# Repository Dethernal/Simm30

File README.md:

* 30 pin 16 MiB Simm module with optional parity chip

Fabrication files can be found in fab_simm30_16 directory.

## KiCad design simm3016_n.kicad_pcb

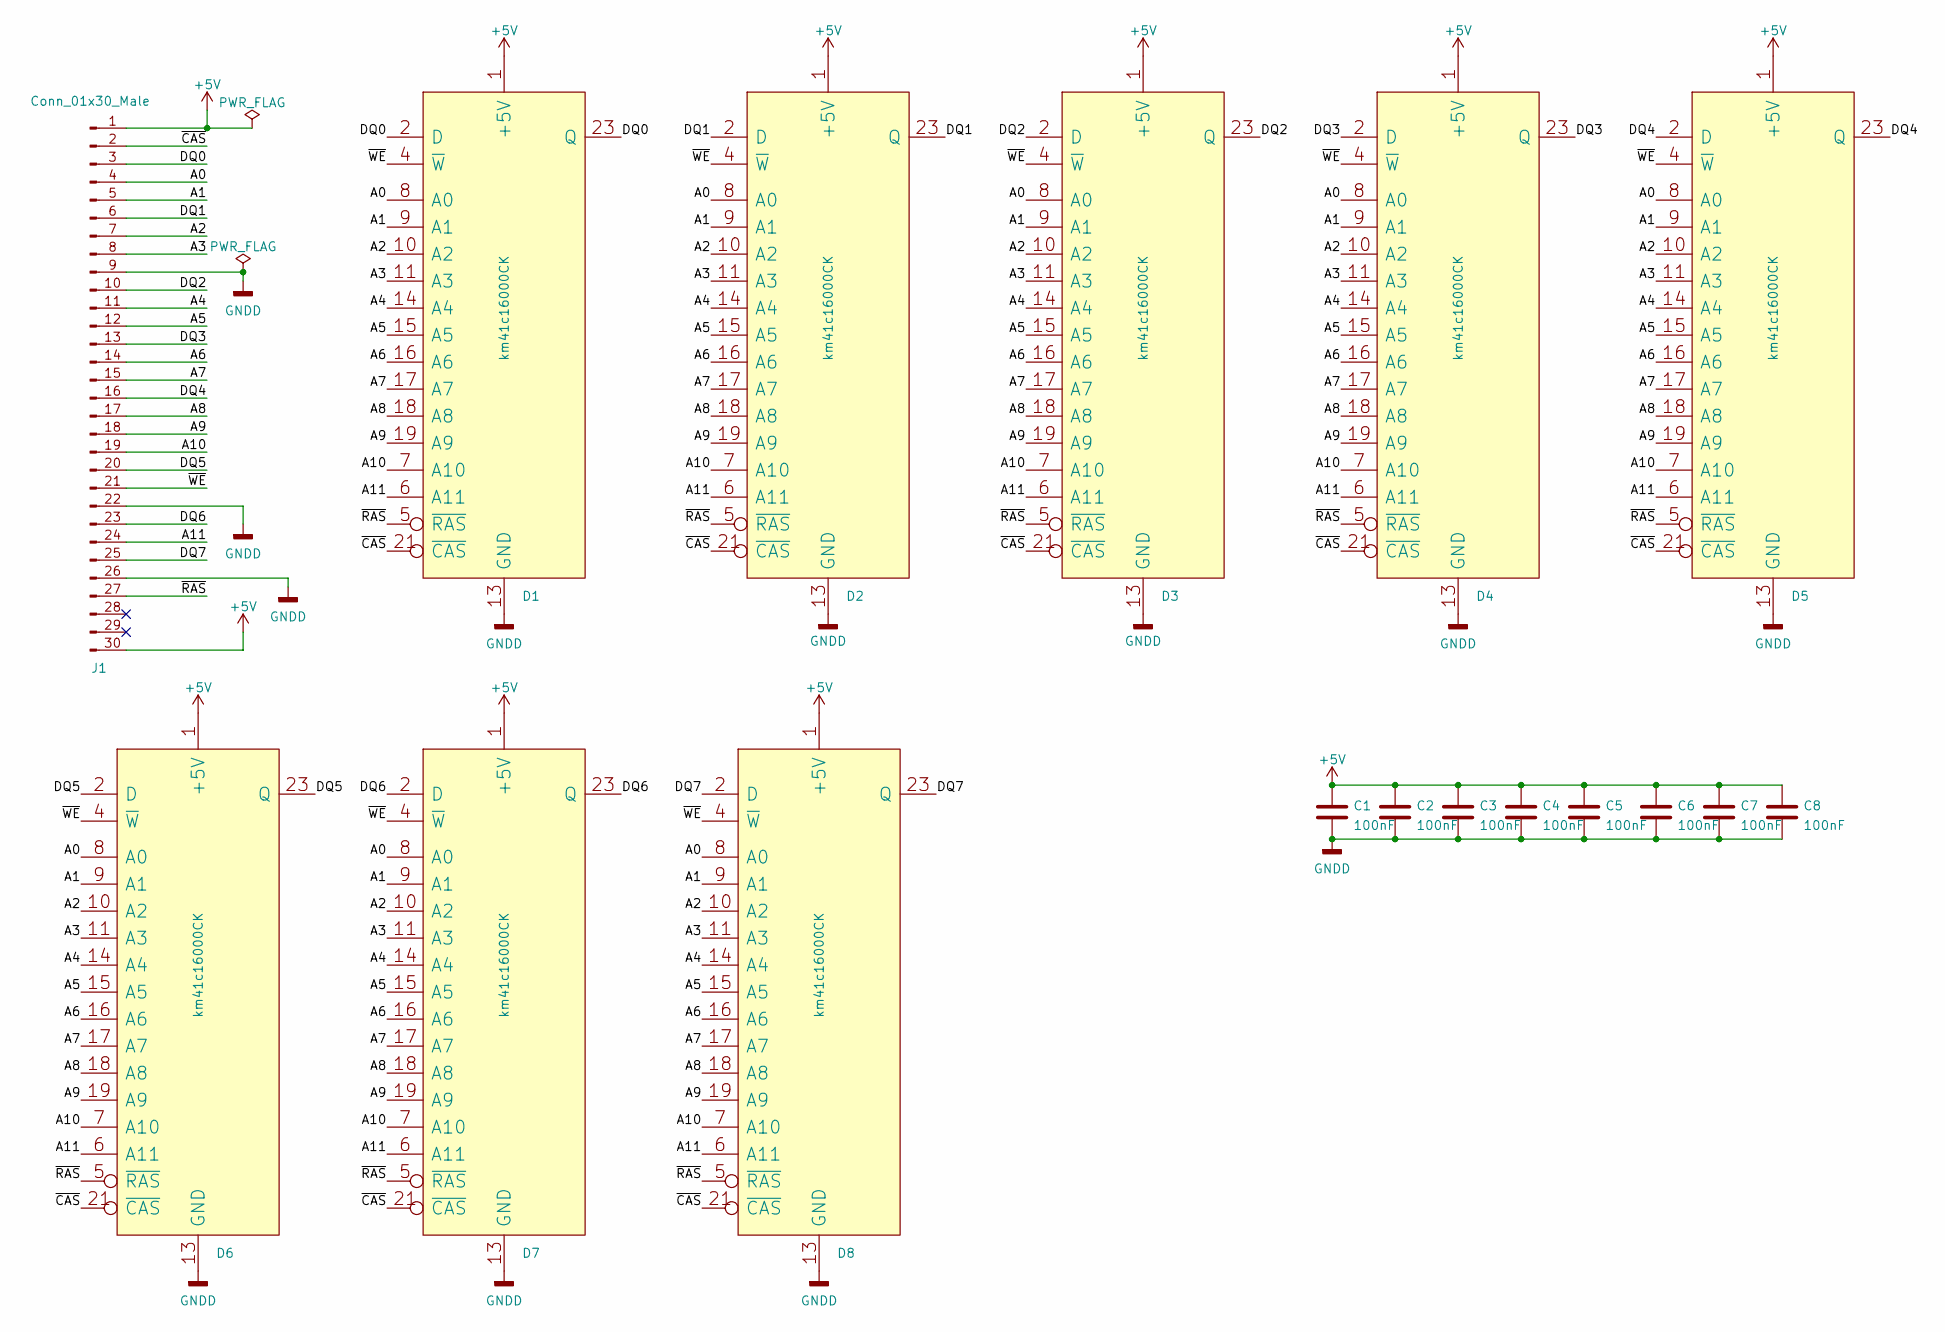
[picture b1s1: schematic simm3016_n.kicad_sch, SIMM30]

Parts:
C1, C2, C3, C4, C5, C6, C7, C8: 100nF; C_0805_2012Metric_Pad1.18x1.45mm_HandSolder
D1, D2, D3, D4, D5, D6, D7, D8: km41c16000CK; SOJ-26-24_7.62x17.14mm_P1.27mm
J1: Conn_01x30_Male; SIMM30_88.86mm_P2.54mm_Edge

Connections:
+5V: C1.1, C2.1, C3.1, C4.1, C5.1, C6.1, C7.1, C8.1, D1.1 (+5V), D2.1 (+5V), D3.1 (+5V), D4.1 (+5V), D5.1 (+5V), D6.1 (+5V), D7.1 (+5V), D8.1 (+5V), J1.1, J1.30
/A0: D1.8 (A0), D2.8 (A0), D3.8 (A0), D4.8 (A0), D5.8 (A0), D6.8 (A0), D7.8 (A0), D8.8 (A0), J1.4
/A1: D1.9 (A1), D2.9 (A1), D3.9 (A1), D4.9 (A1), D5.9 (A1), D6.9 (A1), D7.9 (A1), D8.9 (A1), J1.5
/A2: D1.10 (A2), D2.10 (A2), D3.10 (A2), D4.10 (A2), D5.10 (A2), D6.10 (A2), D7.10 (A2), D8.10 (A2), J1.7
/A3: D1.11 (A3), D2.11 (A3), D3.11 (A3), D4.11 (A3), D5.11 (A3), D6.11 (A3), D7.11 (A3), D8.11 (A3), J1.8
/A4: D1.14 (A4), D2.14 (A4), D3.14 (A4), D4.14 (A4), D5.14 (A4), D6.14 (A4), D7.14 (A4), D8.14 (A4), J1.11
/A5: D1.15 (A5), D2.15 (A5), D3.15 (A5), D4.15 (A5), D5.15 (A5), D6.15 (A5), D7.15 (A5), D8.15 (A5), J1.12
/A6: D1.16 (A6), D2.16 (A6), D3.16 (A6), D4.16 (A6), D5.16 (A6), D6.16 (A6), D7.16 (A6), D8.16 (A6), J1.14
/A7: D1.17 (A7), D2.17 (A7), D3.17 (A7), D4.17 (A7), D5.17 (A7), D6.17 (A7), D7.17 (A7), D8.17 (A7), J1.15
/A8: D1.18 (A8), D2.18 (A8), D3.18 (A8), D4.18 (A8), D5.18 (A8), D6.18 (A8), D7.18 (A8), D8.18 (A8), J1.17
/A9: D1.19 (A9), D2.19 (A9), D3.19 (A9), D4.19 (A9), D5.19 (A9), D6.19 (A9), D7.19 (A9), D8.19 (A9), J1.18
/A10: D1.7 (A10), D2.7 (A10), D3.7 (A10), D4.7 (A10), D5.7 (A10), D6.7 (A10), D7.7 (A10), D8.7 (A10), J1.19
/A11: D1.6 (A11), D2.6 (A11), D3.6 (A11), D4.6 (A11), D5.6 (A11), D6.6 (A11), D7.6 (A11), D8.6 (A11), J1.24
/DQ0: D1.2 (D), D1.23 (Q), J1.3
/DQ1: D2.2 (D), D2.23 (Q), J1.6
/DQ2: D3.2 (D), D3.23 (Q), J1.10
/DQ3: D4.2 (D), D4.23 (Q), J1.13
/DQ4: D5.2 (D), D5.23 (Q), J1.16
/DQ5: D6.2 (D), D6.23 (Q), J1.20
/DQ6: D7.2 (D), D7.23 (Q), J1.23
/DQ7: D8.2 (D), D8.23 (Q), J1.25
/~CAS: D1.21 (~CAS), D2.21 (~CAS), D3.21 (~CAS), D4.21 (~CAS), D5.21 (~CAS), D6.21 (~CAS), D7.21 (~CAS), D8.21 (~CAS), J1.2
/~RAS: D1.5 (~RAS), D2.5 (~RAS), D3.5 (~RAS), D4.5 (~RAS), D5.5 (~RAS), D6.5 (~RAS), D7.5 (~RAS), D8.5 (~RAS), J1.27
/~WE: D1.4 (~W), D2.4 (~W), D3.4 (~W), D4.4 (~W), D5.4 (~W), D6.4 (~W), D7.4 (~W), D8.4 (~W), J1.21
GNDD: C1.2, C2.2, C3.2, C4.2, C5.2, C6.2, C7.2, C8.2, D1.13 (GND), D2.13 (GND), D3.13 (GND), D4.13 (GND), D5.13 (GND), D6.13 (GND), D7.13 (GND), D8.13 (GND), J1.9, J1.22, J1.26

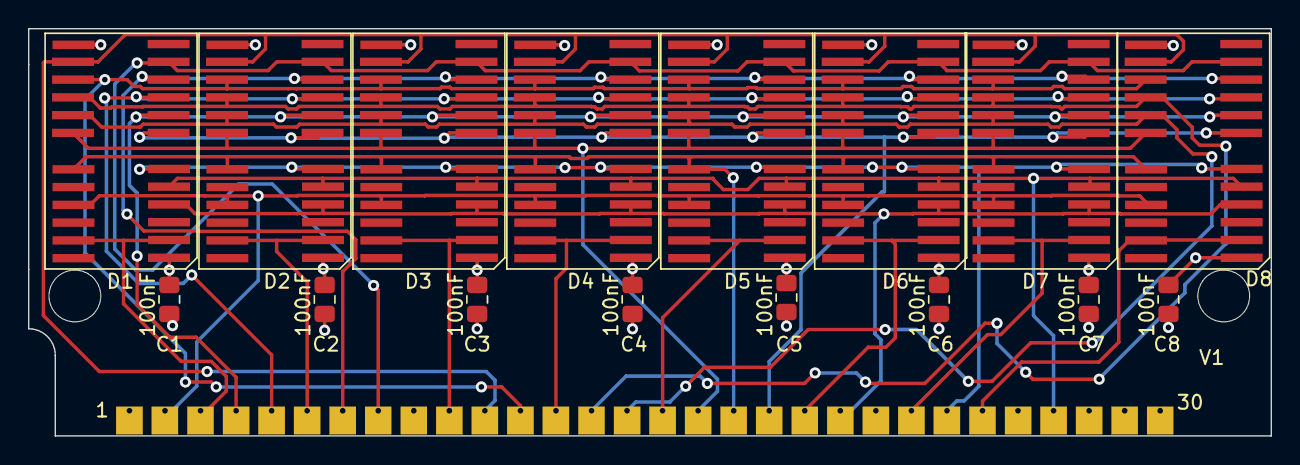
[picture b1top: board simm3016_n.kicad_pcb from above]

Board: 4 copper layers, 88.8 x 29.1 mm, 18 parts (1 on the bottom side), 25 nets.

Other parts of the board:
LOGO: OSHW-Logo2_9.8x8mm_SilkScreen

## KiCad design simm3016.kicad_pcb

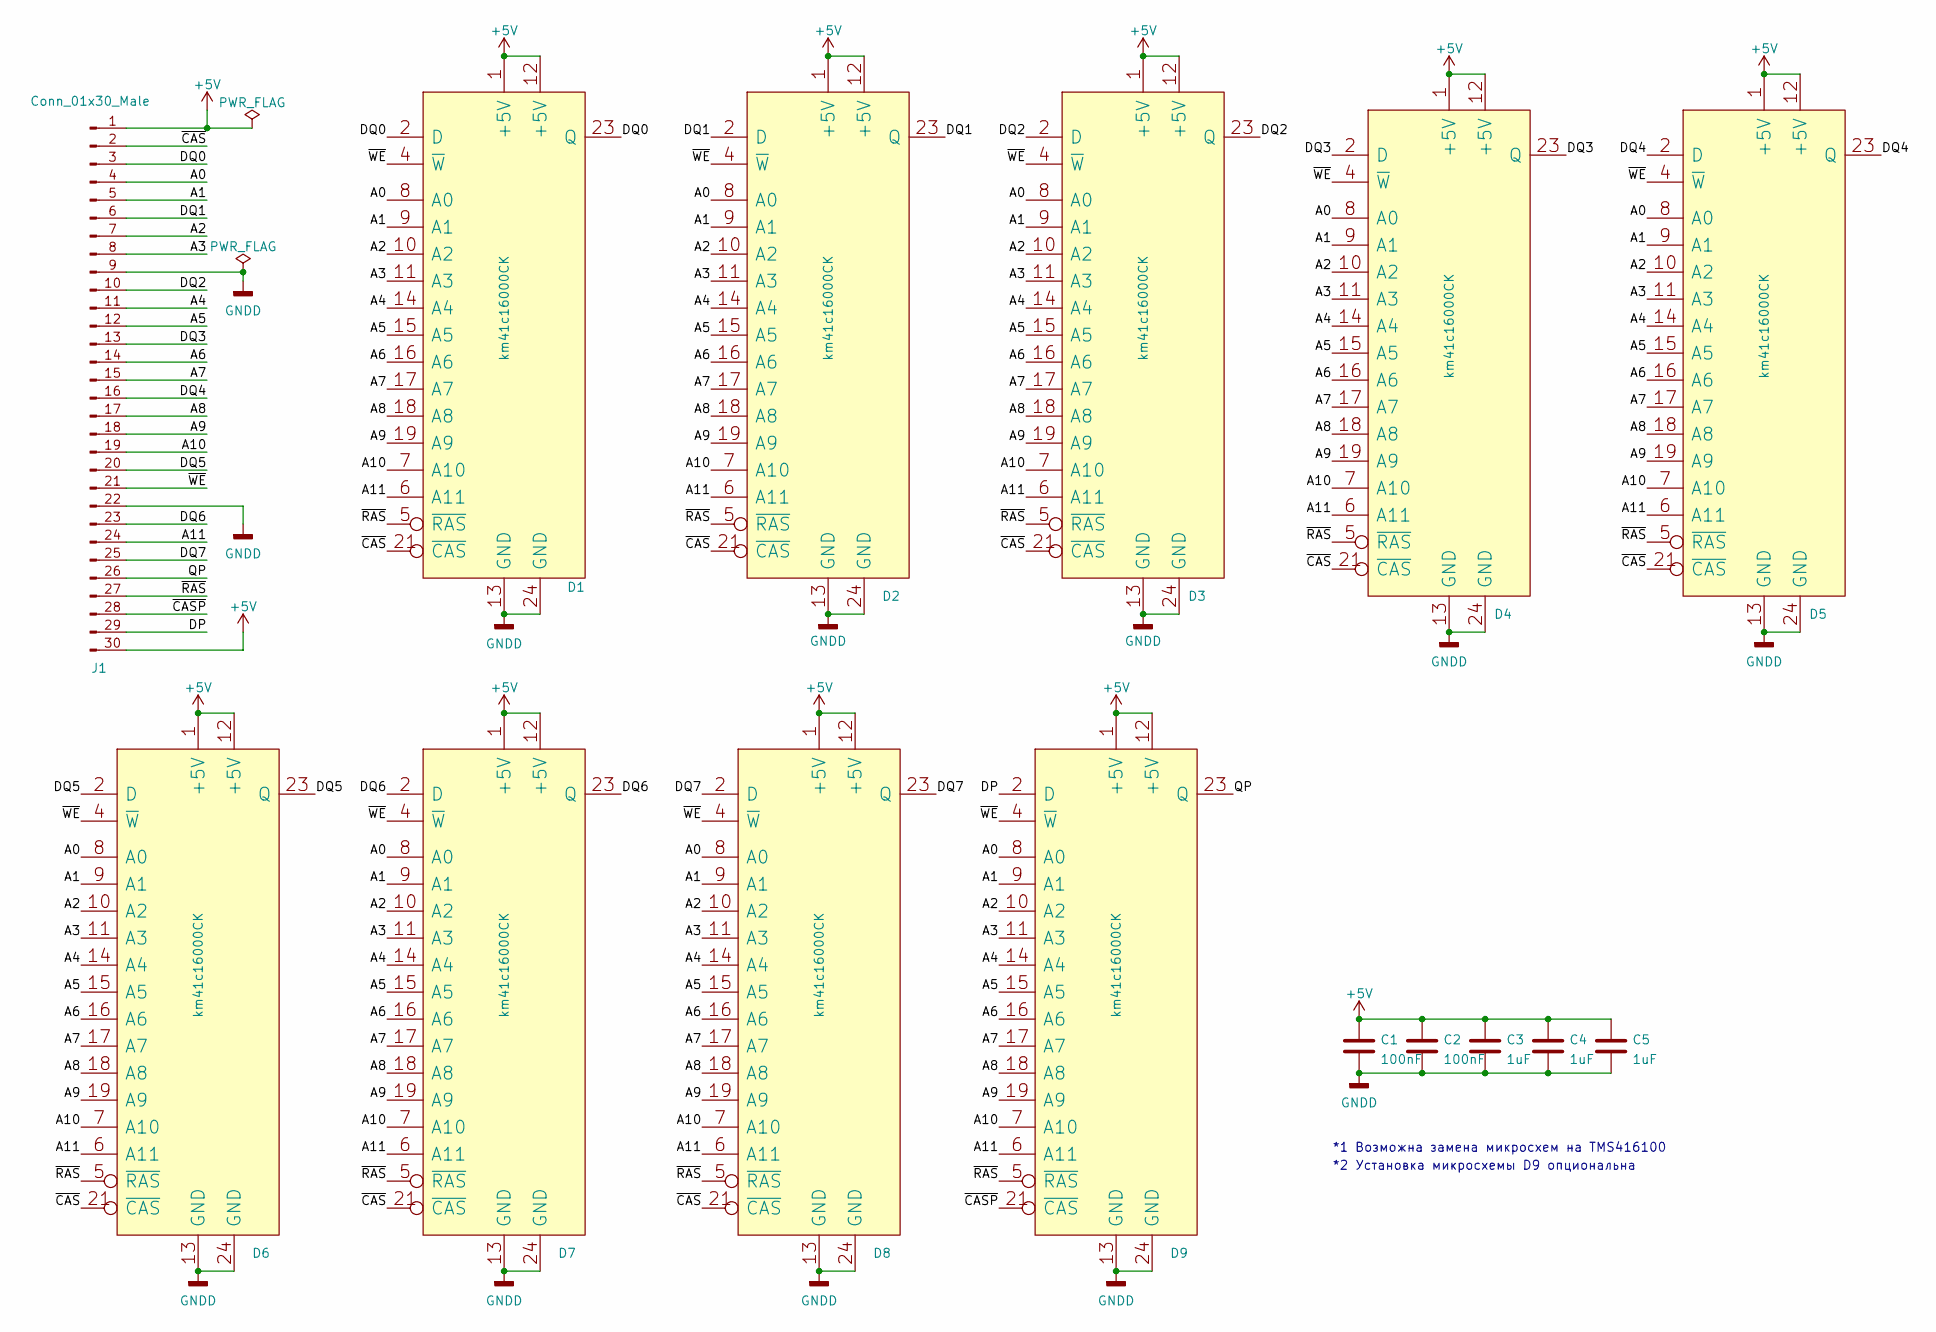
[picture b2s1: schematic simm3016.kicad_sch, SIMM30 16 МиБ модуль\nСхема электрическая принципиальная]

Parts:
C1, C2: 100nF; C_0805_2012Metric_Pad1.18x1.45mm_HandSolder
C3, C4, C5: 1uF; C_0805_2012Metric_Pad1.18x1.45mm_HandSolder
D1, D2, D3, D4, D5, D6, D7, D8, D9: km41c16000CK; SOJ-26-24_7.62x17.14mm_P1.27mm
J1: Conn_01x30_Male; SIMM30_88.86mm_P2.54mm_Edge

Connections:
+5V: C1.1, C2.1, C3.1, C4.1, C5.1, D1.1 (+5V), D1.12 (+5V), D2.1 (+5V), D2.12 (+5V), D3.1 (+5V), D3.12 (+5V), D4.1 (+5V), D4.12 (+5V), D5.1 (+5V), D5.12 (+5V), D6.1 (+5V), D6.12 (+5V), D7.1 (+5V), D7.12 (+5V), D8.1 (+5V), D8.12 (+5V), D9.1 (+5V), D9.12 (+5V), J1.1, J1.30
/A0: D1.8 (A0), D2.8 (A0), D3.8 (A0), D4.8 (A0), D5.8 (A0), D6.8 (A0), D7.8 (A0), D8.8 (A0), D9.8 (A0), J1.4
/A1: D1.9 (A1), D2.9 (A1), D3.9 (A1), D4.9 (A1), D5.9 (A1), D6.9 (A1), D7.9 (A1), D8.9 (A1), D9.9 (A1), J1.5
/A2: D1.10 (A2), D2.10 (A2), D3.10 (A2), D4.10 (A2), D5.10 (A2), D6.10 (A2), D7.10 (A2), D8.10 (A2), D9.10 (A2), J1.7
/A3: D1.11 (A3), D2.11 (A3), D3.11 (A3), D4.11 (A3), D5.11 (A3), D6.11 (A3), D7.11 (A3), D8.11 (A3), D9.11 (A3), J1.8
/A4: D1.14 (A4), D2.14 (A4), D3.14 (A4), D4.14 (A4), D5.14 (A4), D6.14 (A4), D7.14 (A4), D8.14 (A4), D9.14 (A4), J1.11
/A5: D1.15 (A5), D2.15 (A5), D3.15 (A5), D4.15 (A5), D5.15 (A5), D6.15 (A5), D7.15 (A5), D8.15 (A5), D9.15 (A5), J1.12
/A6: D1.16 (A6), D2.16 (A6), D3.16 (A6), D4.16 (A6), D5.16 (A6), D6.16 (A6), D7.16 (A6), D8.16 (A6), D9.16 (A6), J1.14
/A7: D1.17 (A7), D2.17 (A7), D3.17 (A7), D4.17 (A7), D5.17 (A7), D6.17 (A7), D7.17 (A7), D8.17 (A7), D9.17 (A7), J1.15
/A8: D1.18 (A8), D2.18 (A8), D3.18 (A8), D4.18 (A8), D5.18 (A8), D6.18 (A8), D7.18 (A8), D8.18 (A8), D9.18 (A8), J1.17
/A9: D1.19 (A9), D2.19 (A9), D3.19 (A9), D4.19 (A9), D5.19 (A9), D6.19 (A9), D7.19 (A9), D8.19 (A9), D9.19 (A9), J1.18
/A10: D1.7 (A10), D2.7 (A10), D3.7 (A10), D4.7 (A10), D5.7 (A10), D6.7 (A10), D7.7 (A10), D8.7 (A10), D9.7 (A10), J1.19
/A11: D1.6 (A11), D2.6 (A11), D3.6 (A11), D4.6 (A11), D5.6 (A11), D6.6 (A11), D7.6 (A11), D8.6 (A11), D9.6 (A11), J1.24
/DP: D9.2 (D), J1.29
/DQ0: D1.2 (D), D1.23 (Q), J1.3
/DQ1: D2.2 (D), D2.23 (Q), J1.6
/DQ2: D3.2 (D), D3.23 (Q), J1.10
/DQ3: D4.2 (D), D4.23 (Q), J1.13
/DQ4: D5.2 (D), D5.23 (Q), J1.16
/DQ5: D6.2 (D), D6.23 (Q), J1.20
/DQ6: D7.2 (D), D7.23 (Q), J1.23
/DQ7: D8.2 (D), D8.23 (Q), J1.25
/QP: D9.23 (Q), J1.26
/~CASP: D9.21 (~CAS), J1.28
/~CAS: D1.21 (~CAS), D2.21 (~CAS), D3.21 (~CAS), D4.21 (~CAS), D5.21 (~CAS), D6.21 (~CAS), D7.21 (~CAS), D8.21 (~CAS), J1.2
/~RAS: D1.5 (~RAS), D2.5 (~RAS), D3.5 (~RAS), D4.5 (~RAS), D5.5 (~RAS), D6.5 (~RAS), D7.5 (~RAS), D8.5 (~RAS), D9.5 (~RAS), J1.27
/~WE: D1.4 (~W), D2.4 (~W), D3.4 (~W), D4.4 (~W), D5.4 (~W), D6.4 (~W), D7.4 (~W), D8.4 (~W), D9.4 (~W), J1.21
GNDD: C1.2, C2.2, C3.2, C4.2, C5.2, D1.13 (GND), D1.24 (GND), D2.13 (GND), D2.24 (GND), D3.13 (GND), D3.24 (GND), D4.13 (GND), D4.24 (GND), D5.13 (GND), D5.24 (GND), D6.13 (GND), D6.24 (GND), D7.13 (GND), D7.24 (GND), D8.13 (GND), D8.24 (GND), D9.13 (GND), D9.24 (GND), J1.9, J1.22

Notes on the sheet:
*2 Установка микросхемы D9 опциональна
*1 Возможна замена микросхем на TMS416100

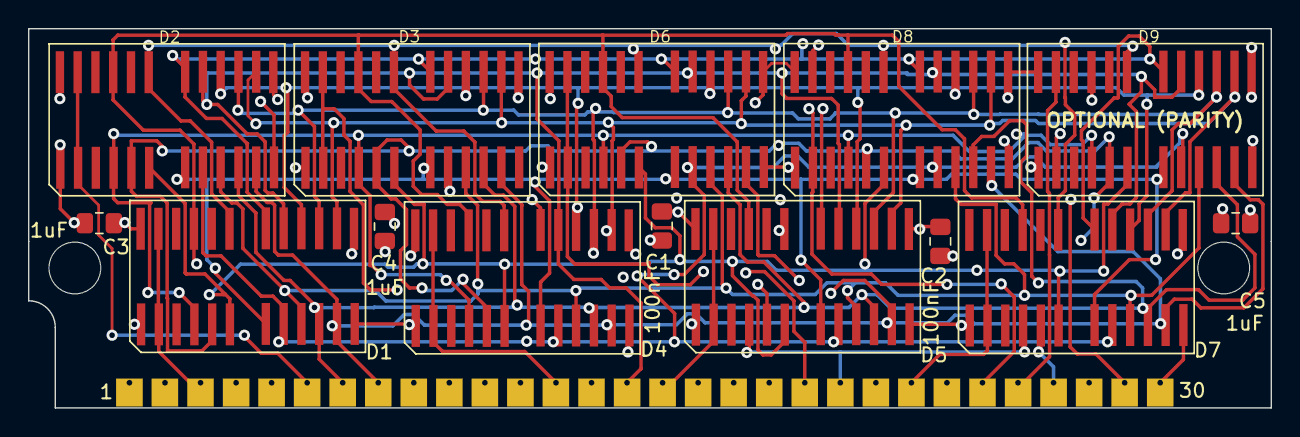
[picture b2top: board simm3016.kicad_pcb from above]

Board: 4 copper layers, 88.8 x 27.1 mm, 15 parts (0 on the bottom side), 28 nets.

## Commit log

2022-07-02 release 1 rev 2
2022-07-02 Update fabrication files
2022-07-02 Update description
2022-07-02 Restore license file
2022-07-02 Remove trash
2022-07-02 Remove old fabrication files
2022-07-02 Added missing 3d packages
